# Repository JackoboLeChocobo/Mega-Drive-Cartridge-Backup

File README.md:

# Mega Drive Cartridge Backup

Fork du projet de X-Death25, auteur originel du projet : https://github.com/X-death25/MD-Dumper

Merci à lui pour les informations sur son projet et pour son aide sur l'utlisation du STM32F401CCU6.

## Objectifs

- Pouvoir récupérer les données de ses propres cartouches Mega Drive

## Outils utilisés

- Système d'exploitation : Debian 12 / Fenikkusu ( Linux )
- Carte de développement STM32F401CCU6 + 3x 74LS273

## Statut du projet 

En attente :

- Réalisation de la carte / Soudure

Etapes Validés :
- Schéma / Typon Kicad réalisés
- Firmware / Logiciel recompilables avec les outils open-source
- Programmeur du STM32F401CCU6 recompilable avec les outils open-source
- Détection du STM32F401CCU6 en tant que "Mega Drive Dumper" sous Linux avec dmesg et le logiciel d'utilisation
- Composants 74LS273 reçus

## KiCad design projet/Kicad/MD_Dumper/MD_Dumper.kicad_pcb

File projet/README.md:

# MD-Dumper

Documentation d'origine du projet par X-death25

What is it ?
-----

MD Dumper is an USB Sega Megadrive cartridge Dumper : <br>
Hardware is based on STM32F4 (BluePillV2) : STM32F4x1 MiniF4 https://github.com/WeActTC/MiniSTM32F4x1  <br>
New version also add some developpement feature witch can be usefull for Megadrive developper.  <br>

Feature :
-----

Firmware Version : 2.0

Software Version : 2.0

| Feature | Implemented |
| ------- | ----------- |
| ROM Dump up to 16 MEG  Classic              | :white_check_mark: |
| ROM Dump up to 32 MEG  Bankswitch           | :white_check_mark: |
| SRAM Backup Memory Classic                  | :white_check_mark: |
| SRAM Backup Memory Bankswitch               | :white_check_mark: |
| Rewrite Krikzz flashkit cart or compatible  | :white_check_mark: |

How to use it ?
-----

You just need an USB-C to USB. <br>
Connect the dumper to the PC and wait blue led activation. Insert game cartridge.  <br>
Start the software. Enjoy ! <br>

Operating System Compatibility
-----

Microsoft Windows 10

Where i can buy it ?
-----

https://www.tindie.com/products/xdeath/md-dumper-usb-megadrive-cartridge-readerwriter/

Linked Repositories
-----

My other projects related to Megadrive Hardware/Software developpement

-=Python MD-Dumper GUI=-
Easy and multiplateform GUI for MD-Dumper <br>
https://github.com/X-death25/PyMD-Dumper

-=DMC Direct Megadrive Connection=-
SGDK lib for bi-directionnal communication between Megadrive and PC <br>
*Coming Soon*

-=SMD_01=-
Simple 5V TTL 8MB Rewritable cartridge for testing code on real hardware <br>
*Coming Soon*

-=X-Flash=-
Altera EPM240 CPLD based Megadrive cartridge used for advanced research <br>
https://github.com/X-death25/X-Flash

Need Help ?
-----
If you need help or want to improvite or report a bug youre welcome to the official MD Dumper Discord !
https://discord.gg/8AtuA29Dnw

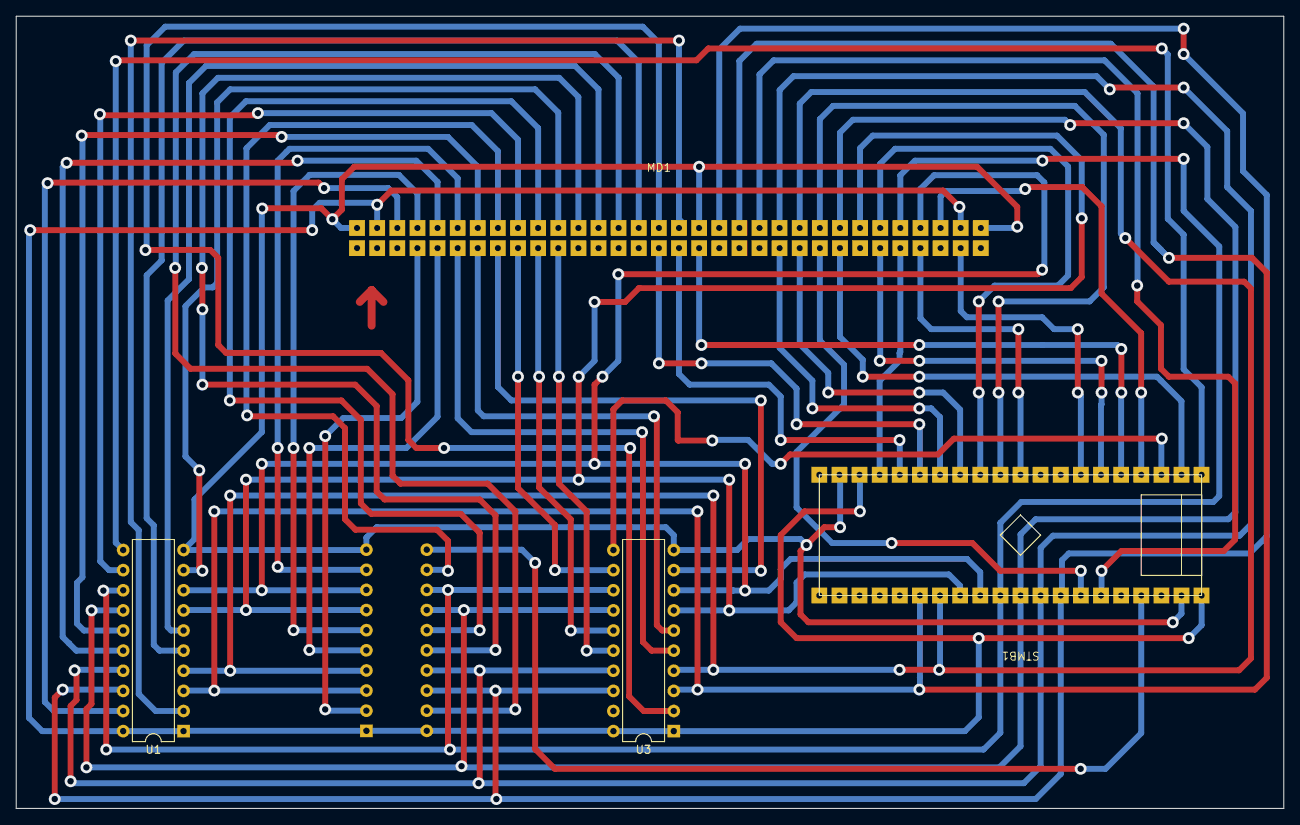
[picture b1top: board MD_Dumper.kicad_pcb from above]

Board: 2 copper layers, 160.0 x 100.0 mm, 5 parts (1 on the bottom side), 51 nets.

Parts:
MD1: Conn_MD
STMB1: STM32F401CCU6 Board
U1, U2, U3: 74LS273; DIP-20_W7.62mm

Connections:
A0: MD1.48 (A17), U1.2 (Q0)
A1: MD1.50 (A15), U1.5 (Q1)
A2: MD1.52 (A13), U1.6 (Q2)
A3: MD1.54 (A11), U1.9 (Q3)
A4: MD1.56 (A09), U1.12 (Q4)
A5: MD1.58 (A07), U1.15 (Q5)
A6: MD1.60 (A05), U1.16 (Q6)
A7: MD1.62 (A03), U1.19 (Q7)
A8: MD1.4 (B04), U2.2 (Q0)
A9: MD1.5 (B05), U2.5 (Q1)
A10: MD1.61 (A04), U2.6 (Q2)
A11: MD1.59 (A06), U2.9 (Q3)
A12: MD1.57 (A08), U2.12 (Q4)
A13: MD1.55 (A10), U2.15 (Q5)
A14: MD1.53 (A12), U2.16 (Q6)
A15: MD1.51 (A14), U2.19 (Q7)
A16: MD1.49 (A16), U3.2 (Q0)
A17: MD1.6 (B06), U3.5 (Q1)
A18: MD1.7 (B07), U3.6 (Q2)
A19: MD1.8 (B08), U3.9 (Q3)
A20: MD1.9 (B09), U3.12 (Q4)
A21: MD1.10 (B10), U3.15 (Q5)
A22: MD1.11 (B11), U3.16 (Q6)
CLK1: STMB1.1 (PB12), U1.11 (Cp)
CLK2: STMB1.37 (PB10), U2.11 (Cp)
CLK3: STMB1.3 (PB14), U3.11 (Cp)
D0_V: MD1.45 (A20), STMB1.26 (PA00), U1.3 (D0), U2.3 (D0), U3.3 (D0)
D1_V: MD1.42 (A23), STMB1.27 (PA01), U1.4 (D1), U2.4 (D1), U3.4 (D1)
D2_V: MD1.39 (A26), STMB1.28 (PA02), U1.7 (D2), U2.7 (D2), U3.7 (D2)
D3_V: MD1.36 (A29), STMB1.29 (PA03), U1.8 (D3), U2.8 (D3), U3.8 (D3)
D4_V: MD1.37 (A28), STMB1.30 (PA04), U1.13 (D4), U2.13 (D4), U3.13 (D4)
D5_V: MD1.40 (A25), STMB1.31 (PA05), U1.14 (D5), U2.14 (D5), U3.14 (D5)
D6_V: MD1.43 (A22), STMB1.32 (PA06), U1.17 (D6), U2.17 (D6), U3.17 (D6)
D7_V: MD1.46 (A19), STMB1.33 (PA07), U1.18 (D7), U2.18 (D7), U3.18 (D7)
D8: MD1.44 (A21), STMB1.35 (PB01)
D9: MD1.41 (A24), STMB1.11 (PB03)
D10: MD1.38 (A27), STMB1.12 (PB04)
D11: MD1.35 (A30), STMB1.4 (PB15)
D12: MD1.25 (B25), STMB1.2 (PB13)
D13: MD1.24 (B24), STMB1.34 (PB00)
D14: MD1.23 (B23), STMB1.13 (PB05)
D15: MD1.22 (B22), STMB1.14 (PB06)
GND: MD1.33 (A32), MD1.47 (A18), MD1.64 (A01), STMB1.19 (GND), STMB1.39 (GND), U1.10 (GND), U2.10 (GND), U3.10 (GND)
MD_AS: MD1.18 (B18), STMB1.5 (PA08)
MD_CE: MD1.17 (B17), STMB1.16 (PB08)
MD_OE: MD1.16 (B16), STMB1.15 (PB07)
MD_RST: MD1.27 (B27), STMB1.6 (PA09)
MD_TIME: MD1.31 (B31), STMB1.7 (PA10)
MD_UWR: MD1.29 (B29), STMB1.10 (PA15)
MD_WE: MD1.28 (B28), STMB1.17 (PB09)
VCC5: MD1.34 (A31), MD1.63 (A02), STMB1.18 (+5V), STMB1.40 (+5V), U1.1 (~Mr), U1.20 (VCC), U2.1 (~Mr), U2.20 (VCC), U3.1 (~Mr), U3.20 (VCC)

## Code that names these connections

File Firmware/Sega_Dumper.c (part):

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#define D7 				GPIO7   									// PA7 	ok
#define ASTRB 			GPIO8  										// PA8 	ok   
#define RST				GPIO9  										// PA9  ok
#define TIME 			GPIO10  									// PA10 ok 
#define UWR				GPIO15  									// PA15 ok 

#define D13 			GPIO0   									// PB0  ok 
#define D8 				GPIO1   									// PB1  ok 	|| WR in DMC Mode
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#define OE 				GPIO7  										// PB7  ok 
#define CE 				GPIO8 										// PB8  ok
#define WE 				GPIO9  										// PB9  ok 
#define CLK2 			GPIO10  	 								// PB10 ok
#define CLK1 			GPIO12  	 								// PB12 ok
#define D12 			GPIO13   									// PB13 ok 
#define CLK3 			GPIO14  	 								// PB14 ok
#define D11 			GPIO15   									// PB15 ok

#define LED_PIN 		GPIO13 										// PC13  STM32 Led

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    gpio_clear(GPIOB,OE);
    gpio_clear(GPIOB,CE);

    gpio_mode_setup(GPIOB,GPIO_MODE_OUTPUT, GPIO_PUPD_NONE,CLK1 | CLK2 | CLK3 );
    gpio_set_output_options(GPIOB,GPIO_OTYPE_PP,GPIO_OSPEED_50MHZ,CLK1 | CLK2 | CLK3 );
    gpio_clear(GPIOB,CLK1);
    gpio_clear(GPIOB,CLK2);
    gpio_clear(GPIOB,CLK3);

    gpio_mode_setup(GPIOC,GPIO_MODE_OUTPUT, GPIO_PUPD_NONE, LED_PIN);

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    setDataOutput();

    DirectWrite8(adr&0xFF);
    gpio_clear(GPIOB,CLK1);
    gpio_set(GPIOB,CLK1);

    DirectWrite8((adr>>8)&0xFF);
    gpio_clear(GPIOB,CLK2);
    gpio_set(GPIOB,CLK2);

    DirectWrite8((adr>>16)&0xFF);
    gpio_clear(GPIOB,CLK3);
    gpio_set(GPIOB,CLK3);
	}

void readMd()  // 0.253 m/s
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    gpio_set(GPIOB,CE);
	gpio_set(GPIOA,ASTRB);
	gpio_set(GPIOA,UWR);
    gpio_set(GPIOB,CLK1);
    gpio_set(GPIOB,CLK2);
    gpio_set(GPIOB,CLK3);
    gpio_set(GPIOB,OE);
	gpio_set(GPIOA,TIME);

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    setDataOutput();

    gpio_set(GPIOB,CE);
    gpio_set(GPIOB,CLK1);
    gpio_set(GPIOB,CLK2);
    gpio_set(GPIOB,CLK3);
    gpio_set(GPIOB,OE);
    gpio_set(GPIOB,WE);

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    setDataOutput();

    gpio_set(GPIOB,CE);
    gpio_set(GPIOB,CLK1);
    gpio_set(GPIOB,CLK2);
    gpio_set(GPIOB,CLK3);
    gpio_set(GPIOB,OE);
    gpio_set(GPIOB,WE);

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	setDataOutput();

    gpio_set(GPIOB,CE);
    gpio_set(GPIOB,CLK1);
    gpio_set(GPIOB,CLK2);
    gpio_set(GPIOB,CLK3);
    gpio_set(GPIOB,OE);
    gpio_set(GPIOB,WE);

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    setDataOutput();

    gpio_set(GPIOB,CE);
    gpio_set(GPIOB,CLK1);
    gpio_set(GPIOB,CLK2);
    gpio_set(GPIOB,CLK3);
    gpio_set(GPIOB,OE);
    gpio_set(GPIOB,WE);

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    setDataOutput();

    gpio_set(GPIOB,CE);
    gpio_set(GPIOB,CLK1);
    gpio_set(GPIOB,CLK2);
    gpio_set(GPIOB,CLK3);
    gpio_set(GPIOB,OE);
    gpio_set(GPIOB,WE);

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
